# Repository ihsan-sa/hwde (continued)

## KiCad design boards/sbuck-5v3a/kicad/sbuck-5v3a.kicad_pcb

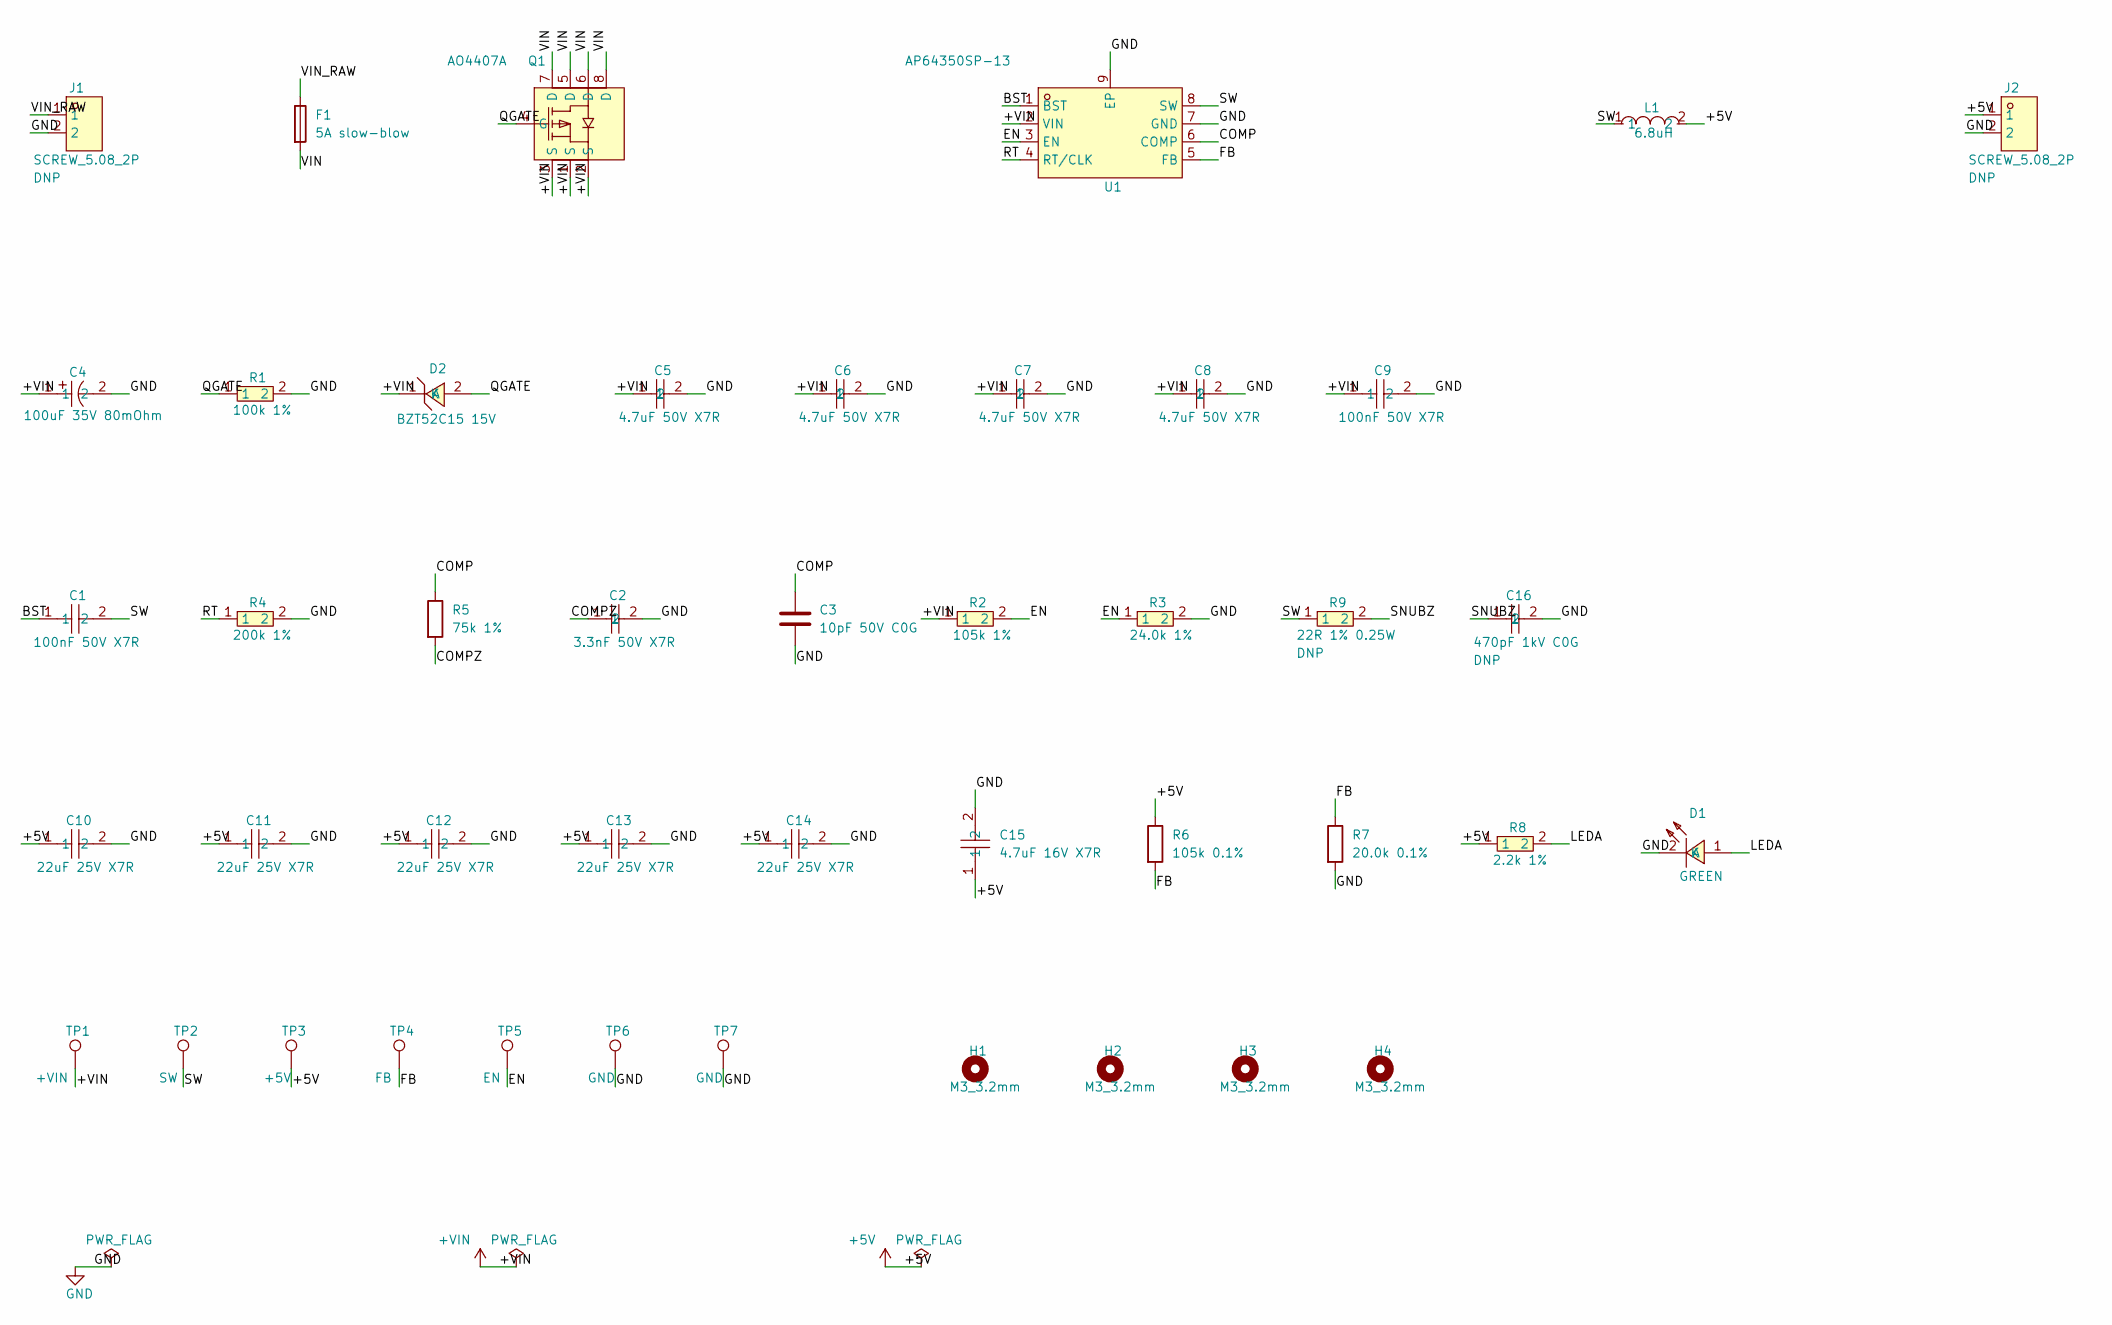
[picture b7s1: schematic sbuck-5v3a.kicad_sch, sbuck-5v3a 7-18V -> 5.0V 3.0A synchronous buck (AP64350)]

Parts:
C1, C9: 100nF 50V X7R; C0603; LCSC C14663
C2: 3.3nF 50V X7R; C0603; LCSC C1613
C3: 10pF 50V C0G; C0603; LCSC C106245
C4: 100uF 35V 80mOhm; CAP-SMD_BD6.3-L6.5-W6.5-LS7.2-FD; LCSC C2982822
C5, C6, C7, C8: 4.7uF 50V X7R; C1206; LCSC C29823
C10, C11, C12, C13, C14: 22uF 25V X7R; C1210; LCSC C49118556
C15: 4.7uF 16V X7R; C0805; LCSC C277499
C16: 470pF 1kV C0G; C1206; LCSC C107177
D1: GREEN; LED0805-R-RD; LCSC C2297
D2: BZT52C15 15V; SOD-123_L2.7-W1.6-LS3.7-RD; LCSC C173427
F1: 5A slow-blow; Fuse_1206_C1T_BelVendorLand; LCSC C3163312
H1, H2, H3, H4: M3_3.2mm; MountingHole_3.2mm_M3
J1, J2: SCREW_5.08_2P; CONN-TH_2P-P5.08_DB128L-5.08-2P; LCSC C395868
L1: 6.8uH; IND-SMD_L11.5-W10.0; LCSC C5298292
Q1: AO4407A; SOIC-8_L4.9-W3.9-P1.27-LS6.0-BL; LCSC C16072
R1: 100k 1%; R0603; LCSC C25803
R2: 105k 1%; R0603; LCSC C16840
R3: 24.0k 1%; R0603; LCSC C23352
R4: 200k 1%; R0603; LCSC C25811
R5: 75k 1%; R0603; LCSC C23242
R6: 105k 0.1%; R0603; LCSC C491109
R7: 20.0k 0.1%; R0603; LCSC C723637
R8: 2.2k 1%; R0603; LCSC C4190
R9: 22R 1% 0.25W; R1206; LCSC C17958
TP1: +VIN; TestPoint_Pad_D1.5mm
TP2: SW; TestPoint_Pad_D1.5mm
TP3: +5V; TestPoint_Pad_D1.5mm
TP4: FB; TestPoint_Pad_D1.5mm
TP5: EN; TestPoint_Pad_D1.5mm
TP6, TP7: GND; TestPoint_Pad_D1.5mm
U1: AP64350SP-13; SO-8_L4.9-W3.9-P1.27-LS6.0-BL-EP; LCSC C2071691

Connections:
+5V: C10.1, C11.1, C12.1, C13.1, C14.1, C15.1, J2.1, L1.2, R6.1, R8.1, TP3.1
+VIN: C4.1, C5.1, C6.1, C7.1, C8.1, C9.1, D2.1 (K), Q1.1 (S), Q1.2 (S), Q1.3 (S), R2.1, TP1.1, U1.2 (VIN)
/BST: C1.1, U1.1 (BST)
/COMP: C3.1, R5.1, U1.6 (COMP)
/COMPZ: C2.1, R5.2
/EN: R2.2, R3.1, TP5.1, U1.3 (EN)
/FB: R6.2, R7.1, TP4.1, U1.5 (FB)
/LEDA: D1.1 (A), R8.2
/QGATE: D2.2 (A), Q1.4 (G), R1.1
/RT: R4.1, U1.4 (RT/CLK)
/SNUBZ: C16.1, R9.2
/SW: C1.2, L1.1, R9.1, TP2.1, U1.8 (SW)
/VIN: F1.2, Q1.5 (D), Q1.6 (D), Q1.7 (D), Q1.8 (D)
/VIN_RAW: F1.1, J1.1
GND: C2.2, C3.2, C4.2, C5.2, C6.2, C7.2, C8.2, C9.2, C10.2, C11.2, C12.2, C13.2, C14.2, C15.2, C16.2, D1.2 (K), J1.2, J2.2, R1.2, R3.2, R4.2, R7.2, TP6.1, TP7.1, U1.7 (GND), U1.9 (EP)

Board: 4 copper layers, 44 parts (0 on the bottom side), 15 nets, no tracks yet.

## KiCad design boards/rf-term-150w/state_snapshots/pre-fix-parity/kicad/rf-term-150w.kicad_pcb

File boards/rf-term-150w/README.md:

# rf-term-150w - 50 ohm / 150 W single-port RF termination, DC-25 MHz

A bolt-down RF dummy load head. The PCB carries the SMA launch, the reactance
trimmer and the mechanical interface only. The 250 W termination element bolts
directly to a heatsink or coldplate you supply; the PCB is deliberately NOT in
the thermal path.

    SMA jack J1 --+-- launch --> R1 tab (element bolts to YOUR heatsink)
                  |
                 C1  trimmer, shunt to ground, tunes out residual reactance

Board: 26.0 x 20.0 mm, 2 layers, 1.6 mm FR4, 1 oz HASL, JLCPCB standard
process (no upcharge options, no controlled impedance).

**Status:** ERC 0/0, DRC 0/0 (routed, parity + all-track-errors + fresh fills),
placement 0/0, DFM pass, simulation pass (4 benches / 295 bounds / 553 measures,
48 build corners). Verification passes with 3 documented waivers - see section 7.
Nothing has been ordered.

---

## 1. Assumptions taken

The brief left two fields blank and told me not to ask. These are the calls I
made; everything downstream depends on them.

| # | Assumption | Why it matters |
|---|---|---|
| A1 | **Fc = 25 MHz**, band DC-25 MHz, spec band 22.5-27.5 MHz | You said "up to 25 MHz". Top of band is worst case for residual reactance. |
| A2 | **Duty = CW, 100 %, continuous** | Duty was blank. CW is the thermally bounding case. **This assumption alone drives the trimmer choice and 72 % of the BOM cost** - see 6. |
| A3 | 25 C ambient, natural convection for the air-cooled figure | Brief specified 25 C ambient. |
| A4 | Element bolts to your heatsink; PCB rides beside it on shims | Brief scoped the thermal path out of the design. |
| A5 | Hand-built, 5 off. Not JLC PCBA | All three parts are through-hole / mechanical; PCBA of a bolt-down power part at qty 5 is not sensible. |
| A6 | Shunt trimmer is the reactance null, top-adjustable | Brief required adjustment without desoldering or unbolting. |
| A7 | 50 ohm +/-2 % met by **select-on-test**, not by part tolerance | No >= 250 W flanged RF termination is stocked anywhere at <= 2 %. See 5. |
| A8 | Cost cap reported honestly, not engineered around | The gap is a materials floor, not a sourcing failure. See 6. |
| A9 | Deliverables stop at fab artifacts; nothing ordered | No money spent. |

**The port carries 86.6 Vrms / 122.5 Vpeak / 1.732 Arms.** Every clearance on
this board is set to 0.80 mm from that (IPC-2221, 101-150 V band, row A6 for
exposed lands), not to a default.

---

## 2. Tuning procedure

**Tune at reduced drive or with a VNA. Never at 150 W.** Matching for minimum
reflection is a small-signal measurement and is *more* accurate at low drive.
This keeps you away from a 122.5 Vpeak port entirely. C1's threaded case is
grounded by design, so the metal you touch is at ground potential - that is
defence in depth, not the primary protection.

1. Assemble and bolt down per section 4. Let it reach thermal equilibrium
   **cold** - do not tune a hot load, the tune shifts.
2. Connect a VNA (or a signal source + return-loss bridge / directional
   coupler) to J1 at **<= +10 dBm**. Sweep 20-30 MHz.
3. Insert a **Johanson 8764** tuning tool (0.130 in / 3.30 mm shank,
   non-metallic tip preferred) into C1's top slot. A metal blade detunes the
   reading while inserted - back it out before reading, or use the plastic tool.
4. Turn for **minimum reflection at 25.0 MHz**. It is a genuine interior
   minimum - simulation confirms equal degradation either side of the setting -
   so you will feel it bottom out in both directions rather than run to a stop.
5. Confirm >= 20 dB across 22.5-27.5 MHz **without re-tuning**. Set once at Fc;
   re-optimising per frequency is not what the spec means.
6. Remove the tool, re-read, then apply full power.

### Tuning range

C1 is a Johanson 5602, **1-30 pF**. It is *not* the only capacitance at the
port: the launch (42.5 mm of 0.94 mm trace plus the 5.0 x 7.0 mm lap pad)
contributes **~5.4 pF** of its own. Total in circuit is **6.4-35.4 pF**.

Solved from the true null condition `wC = X/(R^2 + X^2)` (not the `C = L/R^2`
approximation, which is 7 % optimistic at the top of the range) and confirmed
by ngspice:

| C1 setting | Total shunt C | Cancels series X at 25 MHz | Equivalent series L |
|---|---|---|---|
| full CCW (1 pF) | 6.4 pF | 2.520 ohm | **16.04 nH** |
| full CW (30 pF) | 35.4 pF | 15.183 ohm | **96.66 nH** |

> ### Achievable adjustment range: residual series inductance **16.0 nH to 96.7 nH**
> (envelope **14.3-100.3 nH** across the 4.7-6.5 pF parasitic uncertainty band).

**The board sits inside that window on purpose.** Its residual is **19.5 nH**
(band 18.5-23.3), so C1 lands at about **2.4 pF** at 50 ohm - roughly
**0.3-3.3 pF of downward authority and ~26-29 pF upward**. Turning the trimmer
either way makes the match worse, which is what a real null feels like. All 12
resistance x inductance corners were simulated and every one has positive
downward authority at the nominal parasitic; the null was verified as a genuine
interior minimum (Im{Zin} = 3e-7 ohm at the setting, and +/-0.29 pF either side
costs an equal 0.0089 dB).

**This cost nothing.** The RF trace is deliberately *not* routed for minimum
inductance - it is a 33 mm meander at the current-limited minimum width. A true
null beats an over-corrected trimmer stop, so making the launch more inductive
actually *improved* the worst-case return loss by **+1.06 dB**.

**The honest edge.** Under the most conservative convention (all the added
distributed capacitance lumped at the port, 6.1 pF) at 51 ohm or above with the
residual at the low end of its band, C1 bottoms out again. It costs **at most
0.07 dB** and every such build still reads **>= 31.66 dB**. Nothing about the
spec depends on it.

### What the trimmer cannot do

A shunt susceptance only cancels the *imaginary* part. A series residual X
transforms the port resistance to **R_eff = R + X^2/R**, which no amount of
trimming undoes. The 26 dB limit is R_eff <= 55.276 ohm, i.e. X <= 16.24 ohm at
R = 50, or **X <= 12.07 ohm (76.9 nH)** at the +5 % resistance corner. At the
as-routed 19.5 nH (X = 3.06 ohm) the board spends only **30 %** of that budget.

Simulated across 48 builds (4 resistances x 4 parasitics x 3 inductances),
C1 tuned once at 25.0 MHz then frozen across the band:

| Element resistance | RL at 25 MHz | Worst in 22.5-27.5 MHz |
|---|---|---|
| 50.0 ohm (nominal) | 54.6 dB | 52.9 dB |
| 49.0 ohm | 41.6-42.7 dB | 41.2-42.1 dB |
| 51.0 ohm (select-on-test limit) | **38.1-38.8 dB** | 37.7-38.5 dB |
| 52.5 ohm (+5 % catalogue corner) | **31.4-31.7 dB** | **31.3-31.6 dB** |

**Worst point anywhere: 31.43 dB at Fc, 31.27 dB in band**, against specs of
26 dB and 20 dB - margins of **+5.4 dB** and **+11.3 dB**. All 48 builds pass.

Note what holds that margin: at the worst corner the reactance is fully
nulled and what remains is *pure resistance error*. A de-selected +10 % part
reads **26.05 dB**, right on the spec line. **Select-on-test, not tuning, is
what keeps this board in spec.**

This is also why an ordinary "non-inductive" bolt-down power resistor cannot
substitute: at the typical 0.1 uH spec limit, X = 15.71 ohm gives **26.55 dB**
at best and **23.46 dB** with a +5 % part - a spec failure the trimmer cannot
rescue, because it is a *resistive* error by the time it reaches the port.

---

## 3. Thermal - the required heatsink

Element: **Vishay/Barry T50R0-250-12X**, 250 W, thick film on BeO.
Derating curve (datasheet p.1, digitised from the plot's vector path):

    250 W flat from 25 C to 100 C flange, then -5.0 W/C, reaching 0 W at 150 C
    Footnote: "Rating based on <=100 C constant flange temperature"

The curve is defined on **flange** temperature, so the element-to-flange Rth -
which the datasheet does not publish - is not needed to close the requirement.

**150 W is permitted at a flange temperature of 120 C.** Therefore:

> ### Required thermal resistance, flange to ambient, at 150 W and 25 C:
> ## **Rth <= 0.633 C/W**
> (0.500 C/W if you want the part at its 100 %-rated 100 C knee, which leaves
> 100 W of headroom instead of zero.)

**The interface is a third of that budget.** The flange is only 24.77 x 9.525 mm
= 2.359 cm^2. A normal 0.5 C.cm^2/W grease joint is **0.212 C/W**, so:

> ### The heatsink *itself* must be <= 0.421 C/W in free air.
> Quoting 0.633 without this is misleading - mount it dry or sloppy and you
> lose the requirement to the joint alone.

### Derated air-cooled power

Solving the derating curve against a given total Rth:

    P = 250 W                for Rth_total <= 0.30 C/W
    P = 625 / (1 + 5*Rth)    otherwise

With real, currently-purchasable heatsinks (published **natural-convection**
figures, interface included):

| Heatsink | Rth_hs | + grease | **CW power** | Flange |
|---|---|---|---|---|
| Wakefield 392-300AB, 300x125x136 mm | 0.33 C/W | 0.542 | **168.5 W** | 116 C |
| Fischer SK 88 100 SA, 100x100x50 mm | 1.05 C/W | 1.262 | **85.5 W** | 133 C |
| No heatsink (bare element in air) | - | - | **~0.8-1.2 W** | - |

> ### Derated air-cooled power: **~85 W** on a sane 100 mm extrusion.
> Hitting the full **150 W in still air needs the 300 mm-class sink** - which
> costs more than every other part on this board combined ($193). Forced air
> reaches 0.42 C/W on a far smaller sink and is the sensible answer if you
> actually need 150 W CW.

---

## 4. Assembly - read before building

The PCB is **not** the thermal path and **not** the ground return by bolting.
Both facts are load-bearing.

1. **Bolt R1 to the heatsink** through its two 3.302 mm flange holes, 18.42 mm
   apart, with a thin, even grease joint. Torque evenly. The board's bottom-edge
   `BOLT CL` and `FLANGE/TAB CL` silk marks give the alignment datum.
2. **Mount the PCB on three 1.0 mm shims** (M3). This lifts top copper to
   2.635 mm, meeting R1's tab underside at 2.667 mm - a 0.032 mm gap, i.e. an
   ideal flat lap solder joint with essentially no added inductance.
   - **Prefer insulating shims** (PEEK / nylon / fibre). They are not needed
     electrically - see 3 below - and they keep the trimmer cooler.
3. **Solder two copper straps from R1's flange to the two GND lands.**
   *This is the only RF return path.* Do not rely on the bolted flange-to-
   heatsink joint: on an anodised sink that joint is a ~418 pF capacitor,
   15.2 ohm at 25 MHz, and the board will not work. Keep the straps short,
   wide and symmetric.
4. **Solder R1's tab to the lap pad.** Guaranteed protrusion is only 3.18 mm
   (the datasheet gives no maximum), so the guaranteed lap is ~2.18 mm -
   measure the actual lead at incoming inspection and trim to suit.
5. **Your heatsink needs a clearance hole under C1**: >= 7 mm diameter,
   >= 5 mm deep or through. C1's threaded case protrudes 4.75 mm below the PCB
   against only 1.0 mm of shim clearance. *Alternative:* let the J1/C1 end of
   the board overhang the heatsink edge - no machining, and it runs cooler.
6. Fit J1 and C1. C1 is top-adjust and must stay reachable with a cable mated.

### Select-on-test (required to meet the DC spec)

The specified element is **+/-5 % catalogue** - no >= 250 W flanged RF
termination is stocked anywhere at <= 2 %, and this part number has no
tolerance suffix at all. So the 50 ohm +/-2 % requirement is met by
**measuring and selecting**:

> 4-wire measure each element. **Accept 49.00-51.00 ohm.** Order spares -
> the datasheet only guarantees +/-5 %, so some parts will fall outside.

This is doing real work: resistance tolerance, not layout inductance, is the
entire error budget. A 3x change in inductance moves return loss by <1 dB; the
+5 % resistance step costs 40 dB.

---

## 5. Safety

- **BeO (beryllium oxide) substrate on R1.** Toxic if inhaled as dust.
  **Do not machine, grind, drill, sand or break the part.** Intact and bolted
  down it is safe. An AlN-substrate drop-in (Barry TA50R0-300-2X, dimensionally
  identical) is documented but was out of stock at both distributors.
- **Hot surface in normal operation.** The flange runs 100-133 C at rated
  power - this is the design condition, not a fault. Do not touch. Allow
  cool-down before handling.
- **>30 V.** 122.5 Vpeak at the port. Never tune at full power; see 2.
- **Never key the transmitter with the port unmated.**
- **No protection of any kind.** This is a bare passive load: no fusing, no
  over-temperature cutout, no interlock, no VSWR trip, no enclosure. If it is
  driven beyond the derated power for its heatsink, nothing intervenes -
  the element runs up its derating curve until it fails. Provide external
  protection if the driving source can exceed the rating.
- **R1's datasheet publishes no maximum voltage or current rating at all.**
  The 86.6 Vrms / 1.732 Arms operating point is inferred from the 250 W power
  rating into 50 ohm, not read off a limit line. Do not assume headroom.
- **SMA is a low-mating-cycle connector** (typically a few hundred cycles, not
  published for this part). For a load that gets moved between rigs often,
  expect the jack to wear out before anything else does.

---

## 6. BOM and cost - the brief's $40 cap is not achievable

Qty-5 pricing, distributor-verified.

| Ref | Part | Source | Qty 5 | Ea. | Ext. |
|---|---|---|---|---|---|
| R1 | Vishay/Barry **T50R0-250-12X**, 50 ohm 250 W BeO flanged | DigiKey 4353-T50R0-250-12X-ND | 5 | $24.40 | $122.00 |
| C1 | Johanson **5602**, 1-30 pF 250 V air trimmer, -65/+125 C | DigiKey 1956-1000-ND | 5 | $63.37 | $316.85 |
| J1 | Lian Xin **SMA-KWE**, SMA jack, 335 Vrms | LCSC C7498154 | 5 | $0.561 | $2.81 |
| | PCB, 2L 26x20 mm | JLCPCB | 5 | - | ~$2-6 |
| | | | | **Total** | **~$444** |

> **~$444 against a $40 cap - about 11x.** Reported, not engineered away, per
> the brief's own instruction to keep the design honest.

**Why, and the one lever you have.** Two irreducible costs:

- **R1 ($122)** is a materials floor. 150 W *rated* is not enough: a part rated
  150 W at 25 C flange needs Rth = 0 C/W to pass 150 W at 25 C ambient, which
  is unsatisfiable with any finite heatsink. The element must be >= 250 W class,
  and that means BeO/AlN RF ceramic. Cheaper wirewound "non-inductive" parts
  blow the reactance budget outright.
- **C1 ($317, 72 % of the BOM)** is bought entirely by **assumption A2 (CW)**.

> ### If your duty cycle is not CW, you save $272 per build of 5.
> The cheap alternative is **Vishay BFC280811339**, 3-33 pF, 250 V, ~$8.88 ea
> (LCSC C3273212), which drops total cost to **~$172**. It is rated only
> **-40 to +70 C**, and this board sits at 74-88 C at full 150 W CW - hence the
> expensive part. At reduced duty or reduced CW power it is entirely adequate.
> It needs a different footprint (3-lead vs threaded case), so it is a board
> change, not a drop-in - tell me the real duty and I will respin it.

Counts against the brief's caps: **3 unique BOM lines** (cap 4), **3 placements
/ 6 footprints** (cap 6), **26 x 20 mm** (cap 30 x 30).

---

## 7. Known limits

- **CPL contains 2 rows (C1, J1), not 3.** R1's body is off-board on your
  heatsink; a pick-and-place "position" for it would mislead an assembler. It
  is in the BOM. The board is hand-built anyway.
  Since U3 (2026-08-14) that is a *derived* fact, not a hand-authored one:
  `parts/parts.json` classes R1 `off_board` (with the select-on-test and BeO
  instructions), C1/J1 `smt_placed`, and the mounting hardware
  `customer_supplied`, so `bom_cpl.py` reproduces the delivered `fab/CPL.csv`
  byte-for-byte and emits a `BOM-full.csv` carrying R1 and every instruction.
  `fab/BOM.csv` here stays the HAND-AUTHORED costed BOM (distributor, unit and
  extended price, stock-at-check) - no generator produces those columns, so do
  not overwrite it with a `bom_cpl.py` run into `fab/`; regenerate elsewhere
  and diff. Note C1 is DigiKey-only: `dfm` reports it `dfm_bom_off_lcsc`
  (warning), which is correct - JLC could not fit this board (decision A5).
- **No field solver.** The 19.5 nH residual is a term-by-term geometric budget
  (grounded-CPW model, 0.4281 nH/mm), not a solved EM result. It is swept
  18.5-23.3 nH and the ~5.4 pF launch parasitic is swept 4.7-6.5 pF; every
  simulated bound holds across both bands. The parasitic is an estimate to
  about +/-25 %, not an extraction.
- **The `verify` gate passes only with 3 waivers** (`reports/verify-waivers.json`),
  covering 7 findings. Five are a checker bug - `check_silk.py` treats an
  unfilled rectangle as solid ink, so it reports J1's `(fill no)` body outline
  as covering its own pads; KiCad's own DRC reports zero silk findings on the
  same board. Two are the unavoidable antipads of the /RF through-hole pads in
  the B.Cu pour (0.45 mm of crossing on a 15.065 mm trace). **These were
  approved by the automated run under your no-questions instruction, not by a
  human engineer.**
- **6 silk strokes are 0.12 mm against JLCPCB's 0.15 mm minimum**, inherited
  from the stock KiCad SMA footprint. The DFM gate passes (warning severity);
  JLC may thin or drop those lines. Cosmetic only - the connector's orientation
  is unambiguous from its four symmetric ground legs.
- **J1's 3D model is absent from KiCad**, so mating direction was proven from
  footprint geometry against the vendor drawing rather than from a render.
  **Worth an eyeball before you order.**
- **C1's 6.3 mm plated hole is exactly at JLCPCB's standard limit** (max
  6.3 mm). Compliant, but with zero margin.
- **Rth element-to-flange is absent** from the datasheet, so no element
  temperature is quoted - only flange, which is what the curve is defined on.
- Return loss is verified by simulation and by geometry, **not by measurement**.
  Build one and sweep it.
</content>

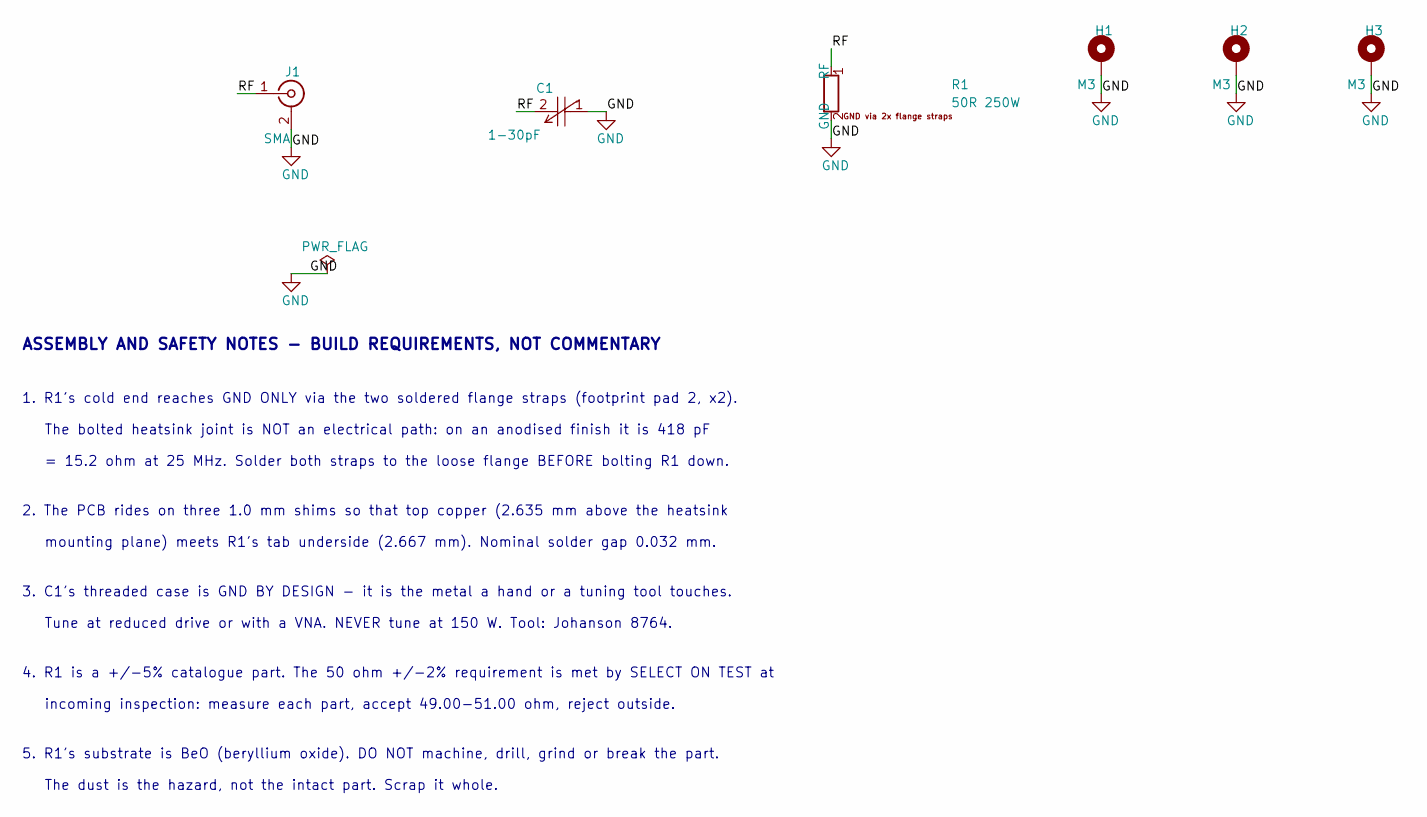
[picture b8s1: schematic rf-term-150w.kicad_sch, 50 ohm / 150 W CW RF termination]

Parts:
C1: 1-30pF; CAP-ADJ-TH_2P-BD7.5_5602; MPN 5602; DigiKey 1956-1000-ND
H1, H2, H3: M3; MountingHole_3.2mm_M3_Pad
J1: SMA; SMA_BAT_Wireless_BWSMA-KWE-Z001; MPN SMA-KWE; LCSC C7498154
R1: 50R 250W; R_LapPad_T50R0-250-12X; MPN T50R0-250-12X; DigiKey 4353-T50R0-250-12X-ND

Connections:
/RF: C1.2 (ROTOR), J1.1 (In), R1.1 (RF)
GND: C1.1 (STATOR), H1.1, H2.1, H3.1, J1.2 (Ext), R1.2 (GND)

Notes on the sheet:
ASSEMBLY AND SAFETY NOTES - BUILD REQUIREMENTS, NOT COMMENTARY
1. R1's cold end reaches GND ONLY via the two soldered flange straps (footprint pad 2, x2).
The bolted heatsink joint is NOT an electrical path: on an anodised finish it is 418 pF
= 15.2 ohm at 25 MHz. Solder both straps to the loose flange BEFORE bolting R1 down.
2. The PCB rides on three 1.0 mm shims so that top copper (2.635 mm above the heatsink
mounting plane) meets R1's tab underside (2.667 mm). Nominal solder gap 0.032 mm.
3. C1's threaded case is GND BY DESIGN - it is the metal a hand or a tuning tool touches.
Tune at reduced drive or with a VNA. NEVER tune at 150 W. Tool: Johanson 8764.
4. R1 is a +/-5% catalogue part. The 50 ohm +/-2% requirement is met by SELECT ON TEST at
incoming inspection: measure each part, accept 49.00-51.00 ohm, reject outside.
5. R1's substrate is BeO (beryllium oxide). DO NOT machine, drill, grind or break the part.
The dust is the hazard, not the intact part. Scrap it whole.

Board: 2 copper layers, 6 parts (0 on the bottom side), 2 nets, no tracks yet.
